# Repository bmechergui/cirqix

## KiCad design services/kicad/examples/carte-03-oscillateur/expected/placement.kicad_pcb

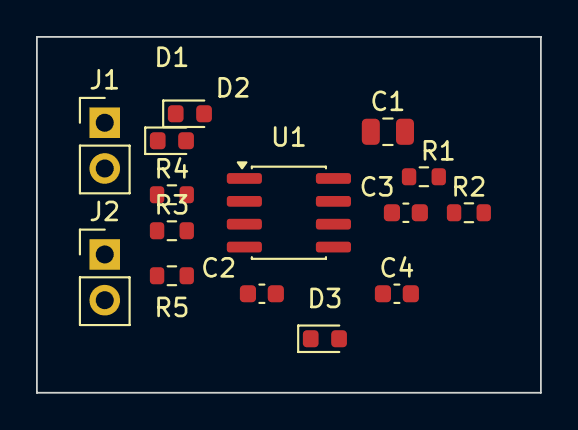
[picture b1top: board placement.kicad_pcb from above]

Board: 2 copper layers, 28.0 x 19.8 mm, 15 parts (0 on the bottom side), 9 nets, no tracks yet.

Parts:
C1: 10uF; C_0805_2012Metric
C2: 100nF; C_0603_1608Metric
C3: 1uF; C_0603_1608Metric
C4: 10nF; C_0603_1608Metric
D1: OUT1; LED_0603_1608Metric
D2: OUT2; LED_0603_1608Metric
D3: OUT3; LED_0603_1608Metric
J1: PWR; PinHeader_1x02_P2.54mm_Vertical
J2: OUT; PinHeader_1x02_P2.54mm_Vertical
R1: 10k; R_0603_1608Metric
R2: 47k; R_0603_1608Metric
R3, R4, R5: 1k; R_0603_1608Metric
U1: NE555; SOIC-8_3.9x4.9mm_P1.27mm

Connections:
CTRL: C4.1, U1.5
DISCH: R1.2, R2.1, U1.7
GND: C1.2, C2.2, C3.2, C4.2, D1.1, D2.1, D3.1, J1.2, J2.2, U1.1
LED1_A: D1.2, R3.2
LED2_A: D2.2, R4.2
LED3_A: D3.2, R5.2
OUT: J2.1, R3.1, R4.1, R5.1, U1.3
THRES: C3.1, R2.2, U1.2, U1.6
VCC: C1.1, C2.1, J1.1, R1.1, U1.4, U1.8

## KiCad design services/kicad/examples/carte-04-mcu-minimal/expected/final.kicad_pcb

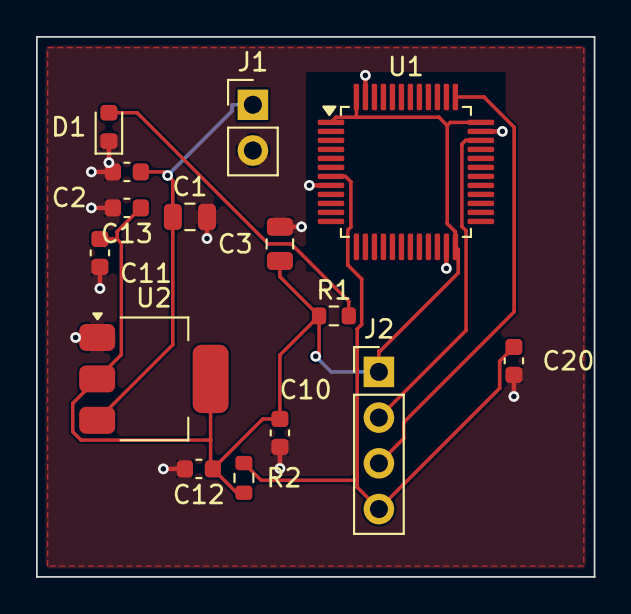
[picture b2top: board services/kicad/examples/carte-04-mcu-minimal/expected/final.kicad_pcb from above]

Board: 2 copper layers, 31.0 x 30.0 mm, 15 parts (0 on the bottom side), 7 nets.

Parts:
C1, C3: 10uF; C_0805_2012Metric
C2, C10, C11, C12, C13, C20: 100nF; C_0603_1608Metric
D1: PWR; LED_0603_1608Metric
J1: IN_5V; PinHeader_1x02_P2.54mm_Vertical
J2: SWD; PinHeader_1x04_P2.54mm_Vertical
R1: 1k; R_0603_1608Metric
R2: 10k; R_0603_1608Metric
U1: STM32F103C8T6; LQFP-48_7x7mm_P0.5mm
U2: AMS1117-3.3; SOT-223-3_TabPin2

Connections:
+3V3: C3.1, C10.1, C11.1, C12.1, C13.1, J2.1, R1.1, R2.2, U1.1, U1.24, U1.36, U1.48, U2.2
GND: C1.2, C2.2, C3.2, C10.2, C11.2, C12.2, C13.2, C20.2, D1.1, J1.2, U1.8, U1.23, U1.35, U1.47, U2.1
LED_PWR: D1.2, R1.2
NRST: C20.1, J2.4, R2.1, U1.7
SWCLK: J2.3, U1.37
SWDIO: J2.2, U1.34
VIN: C1.1, C2.1, J1.1, U2.3

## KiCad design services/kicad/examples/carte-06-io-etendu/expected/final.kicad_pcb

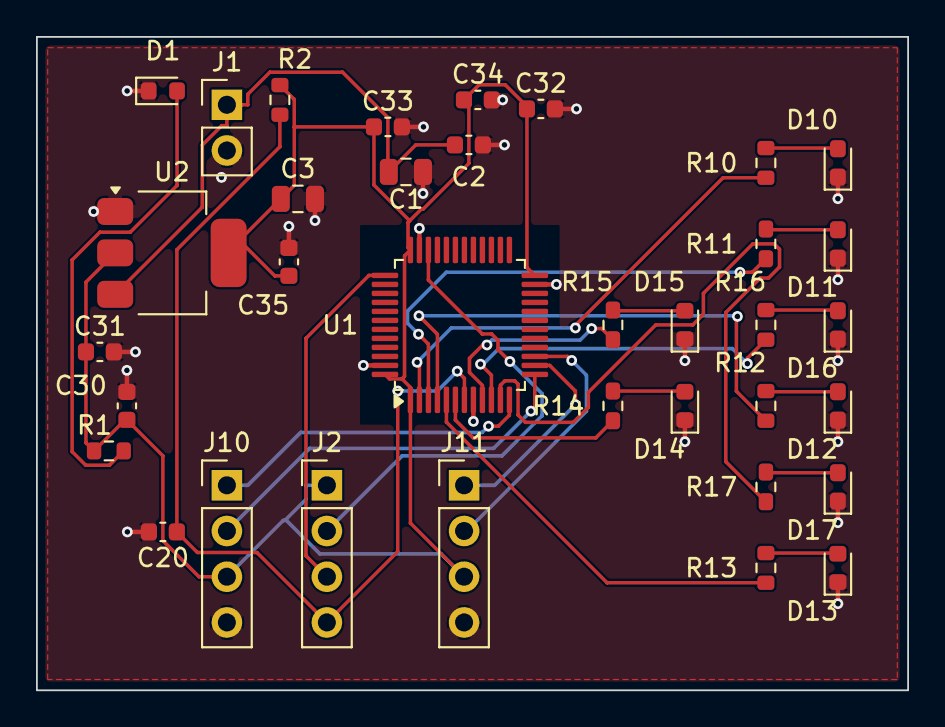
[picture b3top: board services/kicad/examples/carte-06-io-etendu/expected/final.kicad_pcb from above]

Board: 2 copper layers, 48.4 x 36.3 mm, 35 parts (0 on the bottom side), 27 nets.

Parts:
C1, C3: 10uF; C_0805_2012Metric
C2, C20, C30, C31, C32, C33, C34, C35: 100nF; C_0603_1608Metric
D1: PWR; LED_0603_1608Metric
D10, D11, D12, D13, D14, D15, D16, D17: LED; LED_0603_1608Metric
J1: IN_5V; PinHeader_1x02_P2.54mm_Vertical
J2: SWD; PinHeader_1x04_P2.54mm_Vertical
J10: IO0; PinHeader_1x04_P2.54mm_Vertical
J11: IO1; PinHeader_1x04_P2.54mm_Vertical
R1, R10, R11, R12, R13, R14, R15, R16, R17: 1k; R_0603_1608Metric
R2: 10k; R_0603_1608Metric
U1: STM32F103C8T6; LQFP-48_7x7mm_P0.5mm
U2: AMS1117-3.3; SOT-223-3_TabPin2

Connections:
+3V3: C3.1, C30.1, C31.1, C32.1, C33.1, C34.1, C35.1, J2.1, J10.3, J11.3, R1.1, R2.2, U1.1, U1.24, U1.36, U1.48, U2.2
EXT0_1: J10.1, U1.12
EXT0_2: J10.2, U1.13
EXT1_1: J11.1, U1.14
EXT1_2: J11.2, U1.15
GND: C1.2, C2.2, C3.2, C20.2, C30.2, C31.2, C32.2, C33.2, C34.2, C35.2, D1.1, D10.1, D11.1, D12.1, D13.1, D14.1, D15.1, D16.1, D17.1, J1.2, J10.4, J11.4, U1.8, U1.23, U1.35, U1.47, U2.1
IO_L0: R10.1, U1.2
IO_L1: R11.1, U1.3
IO_L2: R12.1, U1.4
IO_L3: R13.1, U1.5
IO_L4: R14.1, U1.6
IO_L5: R15.1, U1.9
IO_L6: R16.1, U1.10
IO_L7: R17.1, U1.11
LEDA0: D10.2, R10.2
LEDA1: D11.2, R11.2
LEDA2: D12.2, R12.2
LEDA3: D13.2, R13.2
LEDA4: D14.2, R14.2
LEDA5: D15.2, R15.2
LEDA6: D16.2, R16.2
LEDA7: D17.2, R17.2
LED_PWR: D1.2, R1.2
NRST: C20.1, J2.4, R2.1, U1.7
SWCLK: J2.3, U1.37
SWDIO: J2.2, U1.34
VIN: C1.1, C2.1, J1.1, U2.3

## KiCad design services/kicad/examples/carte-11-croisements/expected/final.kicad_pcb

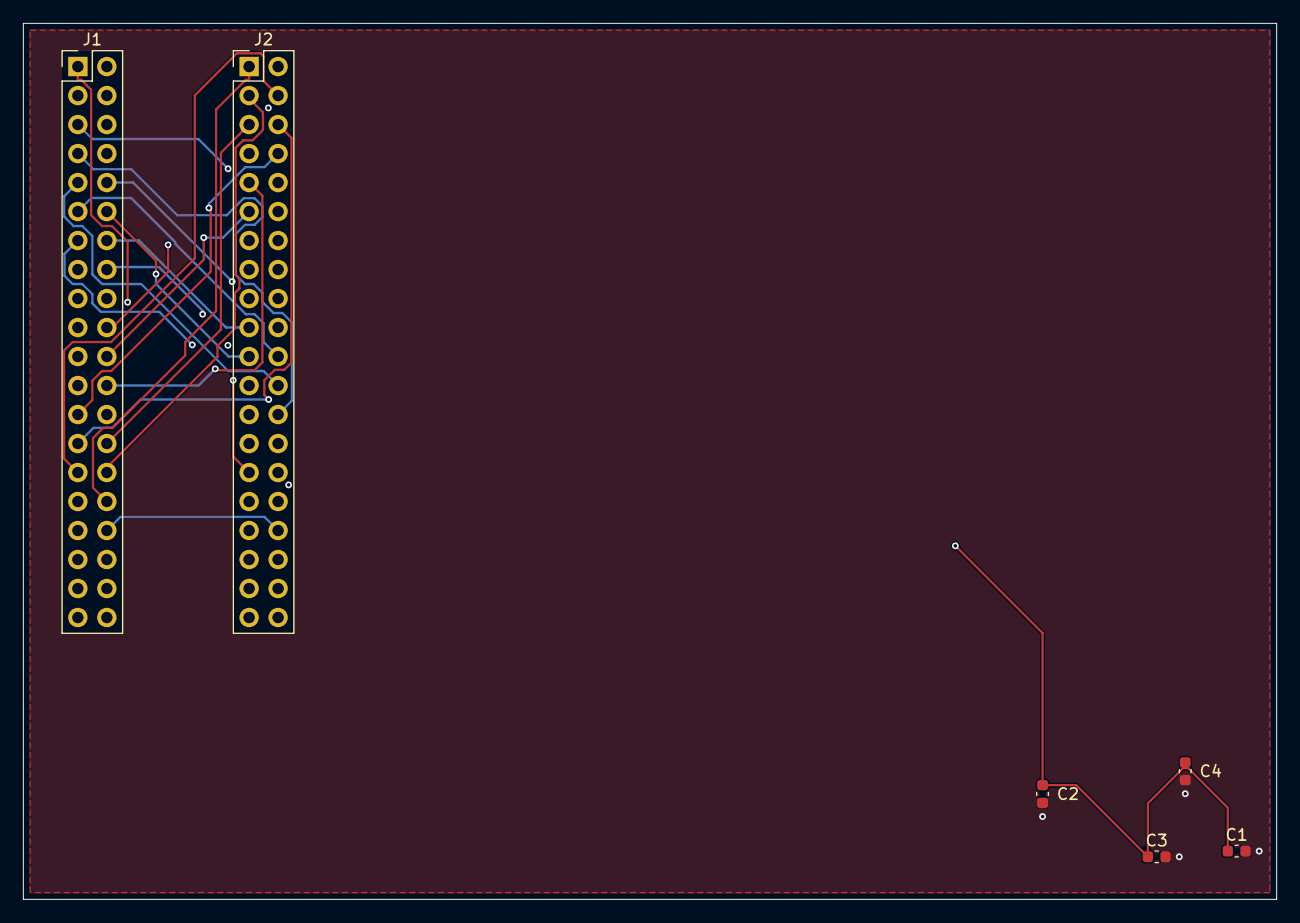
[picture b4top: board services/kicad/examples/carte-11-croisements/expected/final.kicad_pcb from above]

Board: 4 copper layers, 109.8 x 76.7 mm, 6 parts (0 on the bottom side), 34 nets.

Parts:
C1, C2, C3, C4: 100nF; C_0603_1608Metric
J1: BUS_A; PinHeader_2x20_P2.54mm_Vertical
J2: BUS_B; PinHeader_2x20_P2.54mm_Vertical

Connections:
+3V3: C1.1, C2.1, C3.1, C4.1, J1.34, J2.34
GND: C1.2, C2.2, C3.2, C4.2, J1.33, J2.33
X01: J1.1, J2.32
X02: J1.2, J2.31
X03: J1.3, J2.30
X04: J1.4, J2.29
X05: J1.5, J2.28
X06: J1.6, J2.27
X07: J1.7, J2.26
X08: J1.8, J2.25
X09: J1.9, J2.24
X10: J1.10, J2.23
X11: J1.11, J2.22
X12: J1.12, J2.21
X13: J1.13, J2.20
X14: J1.14, J2.19
X15: J1.15, J2.18
X16: J1.16, J2.17
X17: J1.17, J2.16
X18: J1.18, J2.15
X19: J1.19, J2.14
X20: J1.20, J2.13
X21: J1.21, J2.12
X22: J1.22, J2.11
X23: J1.23, J2.10
X24: J1.24, J2.9
X25: J1.25, J2.8
X26: J1.26, J2.7
X27: J1.27, J2.6
X28: J1.28, J2.5
X29: J1.29, J2.4
X30: J1.30, J2.3
X31: J1.31, J2.2
X32: J1.32, J2.1
